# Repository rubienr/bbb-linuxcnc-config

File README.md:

# Introduction
A Linuxcnc configuration using the Panther cape (Necitec).
Since this configuration relys on a new(er than Necitec's supported)
Machinekit/Debian version,
this notes also leave some hints on how to install the Debian image and
compile [Machinekit](http://www.machinekit.io/) on the BBB.

Usage: Checkout the reposigory and start machinekit with the correct arguments, i.e.:

```
machinekit@beaglebone:~$ machinekit <repository-clone>/machinekit/configs/ARM.BeagleBone.Panther/Panther-3-axis.ini
```

# Create Debian Image
1. For creating a bare debian image [follow this steps](https://machinekoder.com/machinekit-debian-stretch-beaglebone-black/).

1. Flash the eMMC contents back to the micro-SD card Insert a micro-SD into your BBB and run:
```
sudo /opt/scripts/tools/eMMC/beaglebone-black-make-microSD-flasher-from-eMMC.sh
```

1. Use/modify this [uEnv.txt](./machinekit/configs/ARM.BeagleBone.Panther/debian/uEnv.txt) template.

1. install and setup [machinekit-deban-stretch](https://machinekoder.com/machinekit-debian-stretch-beaglebone-black/) image

1. setup [lightdm/xfce](https://xpressubuntu.wordpress.com/2014/02/22/how-to-install-a-minimal-ubuntu-desktop/)

1. setup [autologin](https://unix.stackexchange.com/questions/302400/auto-login-on-xfce-in-jessie)

1. Setup the [Necitec](https://www.necitec.de/index.php/de/) Panther cape:
The Panther overlay must be copied from the necitec provided image to
our debian image on the BBB, otherwise **[this](https://github.com/rubienr/bbb-linuxcnc-config/blob/master/machinekit/configs/ARM.BeagleBone.Panther/setup.bridge.sh#L42)**
will fail.
Optional use [this files](https://github.com/rubienr/bbb-linuxcnc-config/tree/master/panther/),
or the [compile and install](https://github.com/rubienr/bbb-linuxcnc-config/tree/master/panther/) script.

Manula way:
```
# optionally compile the source
sudo dtc -O dtb -o /lib/firmware/panther-00A0.dtbo -b 0 -@ /home/machinekit/machinekit/configs/ARM.BeagleBone.Panther/panther-00A0.dts

# copy the compiled file to the debian
/lib/firmware/panther-00A0.dtbo 

# optionally add the overlay to /boot/uEnv.txt
uboot_overlay_addr4=/lib/firmware/panther-00A0.dtbo
```

## References
[Compilation HowTo](https://learn.adafruit.com/introduction-to-the-beaglebone-black-device-tree/compiling-an-overlay)

# Compile Machinekit
## Using BBB and swap Device
1. compile on BBB as far as possible ([Machinekit Developer Howto](http://www.machinekit.io/docs/developing/machinekit-developing/#install-development-packages))

    1. install prerequisites

    1. configure 

    1. make

    1. run machinekit

## Using BBB Without swap Device
Since the compiling process requires more RAM memory as provided by the BBB, it cannot be completed using the BBB only.
In this case we mount the build folder from the BBB via **sshfs** to a **changeroot** on a diffrerent machine.

This rules fail to compile on bbb:

* `make objects/emc/task/emctask.o`
* `make objects/machinetalk/lib/mk_service.o`
* `make objects/emc/task/emctaskmain.o`
* `make objects/emc/task/taskmodule.o`
* `objects/emc/task/taskclass.o`
* `make and so on and so forth...`

Note: An alternative is to swap on MicroSD (if available), which works fine.

The basic steps in a nutshell: 

1. compile on BBB as far as possible ([Machinekit Developer Howto](http://www.machinekit.io/docs/developing/machinekit-developing/#install-development-packages))

    1. install prerequisites
        
    1. configure 
        
    1. make

1. compile the rest in a changeroot

    1. download debian ARM image and changeroot as described in [this repository](https://github.com/rubienr/machinekit-img-chrooting)

    1. install prerequisites as done above

    1. mount the BBB build folder to your changeroot

    1. compile the rest

1. return to your BBB and run machinekit
 
## Rough Procedure Description
1. on beaglebone black

    1. clone repository 
        ````
        machinekit@beaglebone:~$ mkdir ~/git
        machinekit@beaglebone:~/git$ cd ~/git
        machinekit@beaglebone:~/git$ git clone https://github.com/machinekit/machinekit.git
        ````
        
    1. Compile linuxcnc on BBB as far as possible, which means until the compiler crashes due to out of memory.

1. on a different machine

    1. Download and prepare the changeroot as described [here](https://github.com/rubienr/machinekit-img-chrooting).

        ````
        user@host:~/bone-debian-8.7-machinekit-armhf-chroot$ sshfs machinekit@<machinekit-ip>:~/<build-folder>  ./home/machinekit/<build-folder>
        root@host:~/bone-debian-8.7-machinekit-armhf-chroot$ sudo chroot  <path-to-your-chroot> /bin/bash
        root@host:/$ su - machinekit
        (chroot)machinekit@host:~$ cd <build-folder>
        (chroot)machinekit@host:~/git/machinekit$ make
        ````

1. Return to your BBB and proceed further as described in the [Machinekit Developer Howto](http://www.machinekit.io/docs/developing/machinekit-developing/#install-development-packages).

# Tested with 
* Linux beaglebone 4.4.113-ti-rt-r149 #1 SMP PREEMPT RT Fri Apr 6 22:49:25 UTC 2018 armv7l GNU/Linux

# Other References
[start/stop, resume/step halui diagram](https://forum.linuxcnc.org/media/kunena/attachments/16717/Run_StepPause_ResumeLogicDiagram.pdf)

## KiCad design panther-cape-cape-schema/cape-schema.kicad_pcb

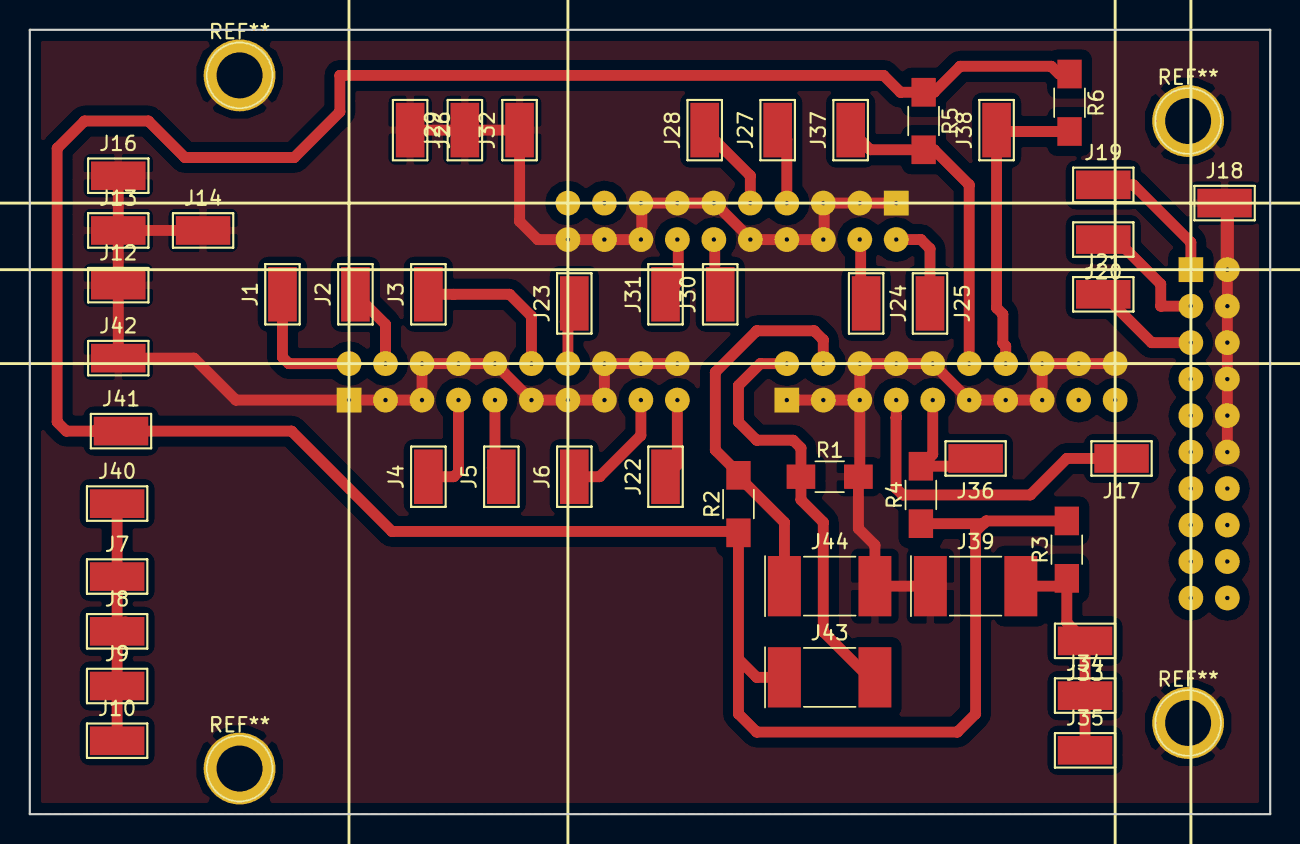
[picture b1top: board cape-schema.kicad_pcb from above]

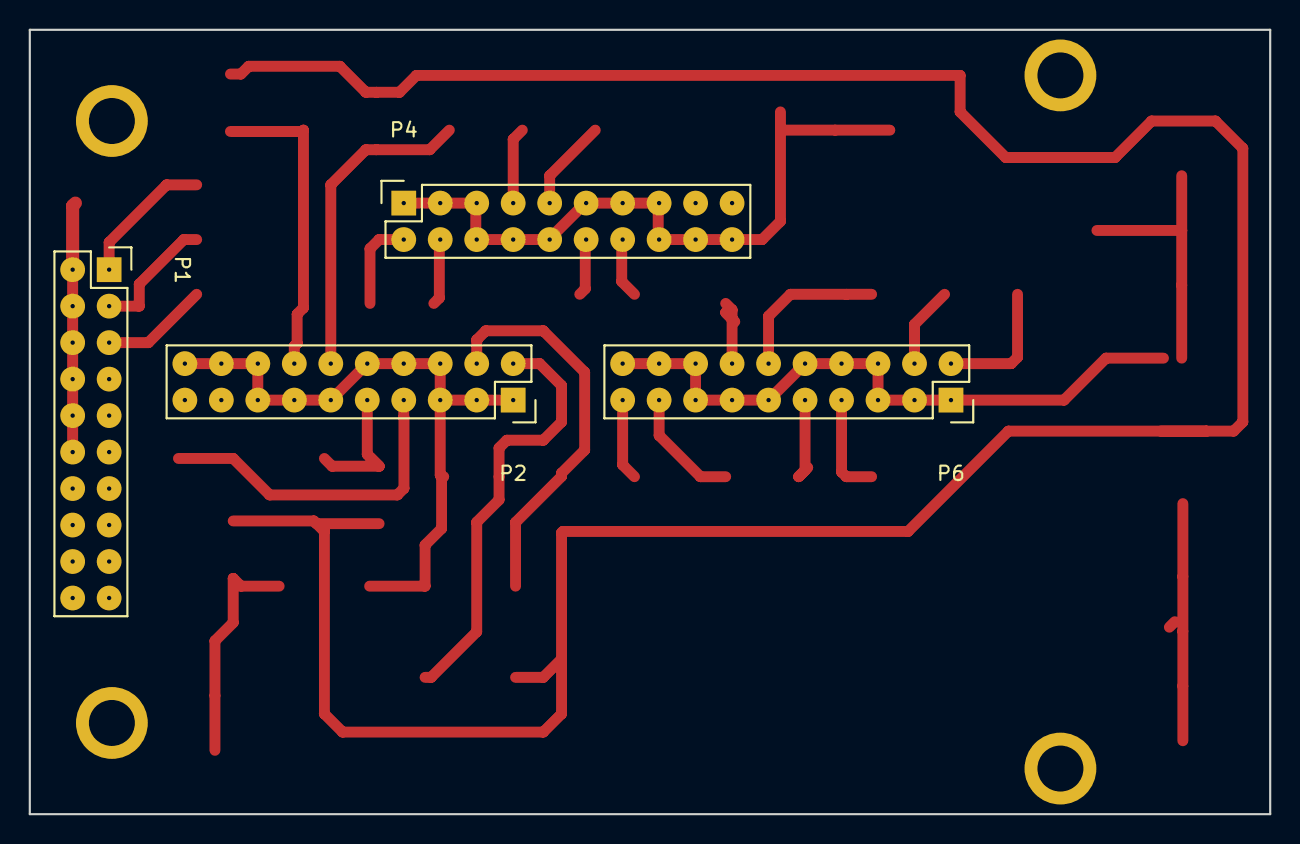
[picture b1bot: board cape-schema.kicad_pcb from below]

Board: 2 copper layers, 86.4 x 54.6 mm, 52 parts (4 on the bottom side), 27 nets.

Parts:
J1: X_LIMIT_MIN; Test_Point_Keystone_5019_Minature
J2: X_LIMIT_MAX; Test_Point_Keystone_5019_Minature
J3: X_HOME; Test_Point_Keystone_5019_Minature
J4: Y_LIMIT_MIN; Test_Point_Keystone_5019_Minature
J5: Y_LIMIT_MAX; Test_Point_Keystone_5019_Minature
J6: Y_HOME; Test_Point_Keystone_5019_Minature
J7, J8, J9, J10, J40: SENSORS+; Test_Point_Keystone_5019_Minature
J12, J13, J14, J16: SENSORS-; Test_Point_Keystone_5019_Minature
J17: SPINDLE_FEEDBACK; Test_Point_Keystone_5019_Minature
J18: SPINDLE_SIGNAL-; Test_Point_Keystone_5019_Minature
J19: SPINDLE_ENABLE; Test_Point_Keystone_5019_Minature
J20: SPINDLE_DIR; Test_Point_Keystone_5019_Minature
J21: SPINDLE_RPM; Test_Point_Keystone_5019_Minature
J22: Z_LIMIT_MIN; Test_Point_Keystone_5019_Minature
J23: Z_LIMIT_MAX; Test_Point_Keystone_5019_Minature
J24: X_DIR; Test_Point_Keystone_5019_Minature
J25: X_STEP; Test_Point_Keystone_5019_Minature
J26, J29, J32: DRIVER_SIGNALS-; Test_Point_Keystone_5019_Minature
J27: Y_STEP; Test_Point_Keystone_5019_Minature
J28: Y_DIR; Test_Point_Keystone_5019_Minature
J30: Z_STEP; Test_Point_Keystone_5019_Minature
J31: Z_DIR; Test_Point_Keystone_5019_Minature
J33, J34, J35: DRIVER_ENABLE; Test_Point_Keystone_5019_Minature
J36: X_ALARM; Test_Point_Keystone_5019_Minature
J37: Y_ALARM; Test_Point_Keystone_5019_Minature
J38: Z_ALARM; Test_Point_Keystone_5019_Minature
J39: DRIVER_ENABLE_SWITCH; Crystal_SMD_MicroCrystal_CC1V-T1A-2pin_8.0x3.7mm
J41: PC+; Test_Point_Keystone_5019_Minature
J42: GND; Test_Point_Keystone_5019_Minature
J43: EMERGENCY_STOP_SWITCH; Crystal_SMD_MicroCrystal_CC1V-T1A-2pin_8.0x3.7mm
J44: Z_PROBE_LIMIT_SWITCH; Crystal_SMD_MicroCrystal_CC1V-T1A-2pin_8.0x3.7mm
P1: OUT2 P4; Socket_Strip_Straight_2x10
P2: IN2 P2; Socket_Strip_Straight_2x10
P4: OUT1 P3; Socket_Strip_Straight_2x10
P6: IN1 P1; Socket_Strip_Straight_2x10
R1: 10k; R_1206_HandSoldering
R2: 20k; R_1206_HandSoldering
R3: 470R; R_1206_HandSoldering
R4, R5, R6: 1k; R_1206_HandSoldering

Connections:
DRIVER_ENABLE: J33.1, J34.1, J35.1, J39.2, R3.1
DRIVER_SIGNALS-: J12.1, J13.1, J14.1, J16.1, J18.1, J26.1, J29.1, J32.1, J39.1, J42.1, J44.2, P1.2, P1.4, P1.6, P1.8, P1.10, P1.12, P2.1, P2.3, P2.5, P2.6, P2.8, P2.10, P2.11, P2.13, P2.15, P2.16, P2.18, P2.20, P4.1, P4.3, P4.5, P4.6, P4.8, P4.10, P4.11, P4.13, P4.15, P4.16, P4.18, P4.20, P6.1, P6.3, P6.5, P6.6, P6.8, P6.10, P6.11, P6.13, P6.15, P6.16, P6.18, P6.20, R1.2
EMERGENCY_STOP: J43.2, P2.2, R1.1
PC+: J41.1, J43.1, R2.1, R3.2, R4.1, R5.1, R6.1
SENSORS+: J7.1, J8.1, J9.1, J10.1, J40.1
SPINDLE_DIR: J20.1, P1.3
SPINDLE_ENABLE: J19.1, P1.1
SPINDLE_RPM: J21.1, P1.5
SPINDLE_RPM_FEEDBACK: J17.1, P2.7
X_ALARM: J36.1, P2.9, R4.2
X_DIR: J24.1, P4.4
X_HOME: J3.1, P6.12
X_LIMIT_MAX: J2.1, P6.4
X_LIMIT_MIN: J1.1, P6.2
X_STEP: J25.1, P4.2
Y_ALARM: J37.1, P2.12, R5.2
Y_DIR: J28.1, P4.9
Y_HOME: J6.1, P6.17
Y_LIMIT_MAX: J5.1, P6.9
Y_LIMIT_MIN: J4.1, P6.7
Y_STEP: J27.1, P4.7
Z_ALARM: J38.1, P2.14, R6.2
Z_DIR: J31.1, P4.14
Z_LIMIT_MAX: J23.1, P6.14
Z_LIMIT_MIN: J22.1, P6.19
Z_PROBE: J44.1, P2.4, R2.2
Z_STEP: J30.1, P4.12

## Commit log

2017-05-26 initial import
2017-05-27 set homing to non volatile
2017-05-27 added .bashrc
2017-05-27 added information regarding manually installed packages
2017-05-28 updated readme after having debian 8.8 experience
2017-07-24 minor changes
2017-07-29 updated documentation
2017-07-29 minor chagnes
2017-07-29 added necitec panther cape device tree overlay
2017-07-29 added preliminary cnc schema
2017-07-29 removed unnecessary libs
2017-07-30 updated schema
2017-07-30 finalized schema
2017-07-30 refined schema
2017-08-02 minor schema changes
2017-08-06 corrected many labels, removed and driectly connected switches to panther conn.
2017-08-06 added ppp-pahtner-cape's cape schema
2017-08-15 routed single layer pcb
2017-08-19 added mounting holes
2017-08-20 added missing footprint library
2017-08-20 updated hal: spindle pwm, drivers' alarm, estop
2017-08-20 fixed connector naming mismatch
2017-08-27 added xhc-whb04b-6 tcl files
2017-08-27 prepared ini file for jog dial
2017-08-28 fixed pin invert syntax issue
2017-08-28 deleted unnecessary file
2017-08-28 replaced tcl files by symlinks to machinekit source folder (temporary hack)
2017-08-28 fixed pid config issue
2017-08-28 patched config (preliminary)
2018-01-03 connected several signals for whb04b-6
2018-01-04 configured buttons: reset, stop, start/resume, m-home, safe-z, w-home, probe-z and homing
2018-01-05 configured all jog dial buttons (whb04b-6), cleanup, added/refined mdi-commands
2018-01-06 configured jog wheel
2018-01-07 fixed spindle configuration issue
2018-01-12 cleanup
2018-01-13 updated motor step (*HOLD delay) and jog dial (ilowpass) parameters
2018-01-13 added configured axis position related signals
2018-01-14 re-structured hal files, configured spindle and feed signals for whb04b-6 jog dial
2018-01-14 updated homing velocities configuration
2018-01-20 updated config. for spindle direction switching and Lead mode
2018-11-25 minor enhancement of nc files
2018-12-03 refined ngc scripts
2018-12-03 migrated file from 3.x to 4.x kernel sysfs entry
2018-12-07 refined necitec panther overlay
2018-12-08 configured huangyang spindle vfd
2018-12-09 enhanced pyvcp vfd pannel to print all available output parameter
2018-12-09 reverted spindle signals
2018-12-09 fixed spindle singal issues with whb pendant and spindle speed display
2018-12-19 configured mklauncher for QtQuickVcp
2018-12-19 intermediate commit: updated kicad projects to v6.0.x
2018-12-20 added launcher script and cleanup
2018-12-29 fine-tuned z-homing
2018-12-29 fixed issue with homing vs machine coordinates button
2018-12-30 removed outdated joint-config
2019-01-14 tuned xyz axis parameters: vel, acc, servo thread and base time
2019-01-24 implemented tool change and enhanced homing: now use max x,y switch instead of home sw
2019-01-24 modified x-homing: now uses x-min switch
2019-01-28 refined tool offset measurement setup and implementation
2021-01-05 refined tool change script
